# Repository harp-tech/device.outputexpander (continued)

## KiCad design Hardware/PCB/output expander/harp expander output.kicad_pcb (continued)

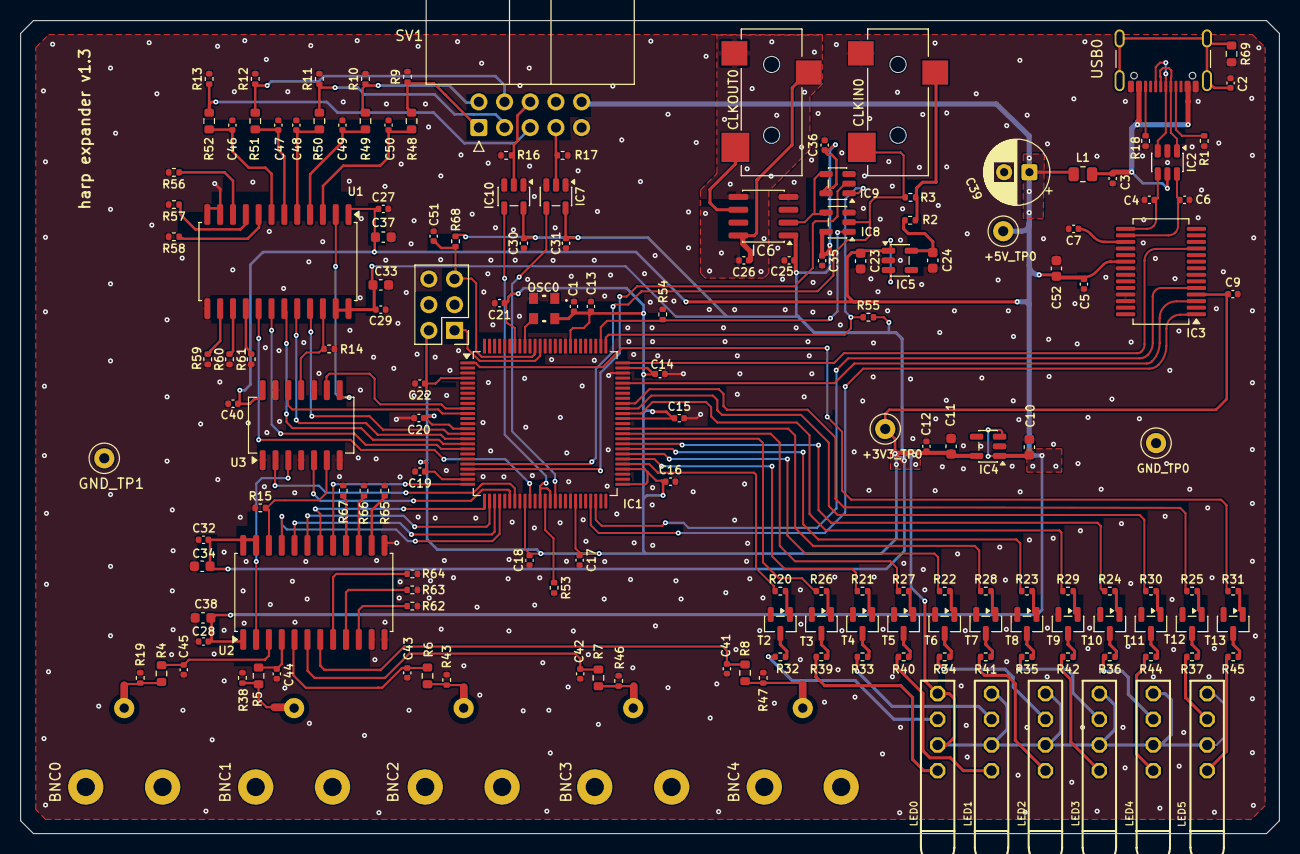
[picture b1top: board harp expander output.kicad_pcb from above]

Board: 2 copper layers, 124.5 x 80.4 mm, 167 parts (0 on the bottom side), 132 nets.

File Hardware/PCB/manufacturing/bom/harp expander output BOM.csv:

"#","Qty","Reference","Value","Tolerance","Footprint","TempCo","Voltage","DNP","OEPSPN","MPN"
"1","5","BNC0,BNC1,BNC2,BNC3,BNC4","731000105","","open-ephys:BNC_MOLEX_0731000105","","","","OEPS070024","731000105"
"2","27","C1,C3,C5,C7,C9,C12,C13,C14,C15,C16,C17,C18,C19,C20,C21,C22,C25,C26,C27,C28,C29,C30,C31,C32,C35,C36,C40","100nF","10%","Capacitor_SMD:C_0402_1005Metric","X7R","50V","","OEPS010016","CGA2B3X7R1H104K050BB"
"3","1","C2","4.7nF","10%","Capacitor_SMD:C_0402_1005Metric","X7R","100V","","OEPS010017","885012205084"
"4","2","C4,C6","47pF","5%","Capacitor_SMD:C_0402_1005Metric","C0G","50V","","OEPS010011","04025A470JAT2A"
"5","9","C10,C11,C23,C24,C33,C34,C37,C38,C52","4.7uF","10%","Capacitor_SMD:C_0603_1608Metric","X6S","16V","","OEPS010018","C1608X6S1C475K080AC"
"6","1","C39","100u","20%","Capacitor_THT:CP_Radial_D6.3mm_P2.50mm","","25V","","OEPS210005","EEU-FM1E101B"
"7","11","C41,C42,C43,C44,C45,C46,C47,C48,C49,C50,C51","330pF","5%","Capacitor_SMD:C_0402_1005Metric","C0G","50V","","OEPS010020","C0402C331J5GAC7867"
"8","2","CLKIN0,CLKOUT0","35RASMT2BHNTRX","","harp_expander_output:35RASMT2BHNTRX","","","","OEPS070025","35RASMT2BHNTRX"
"9","1","IC1","ATXMEGA128A1U-AU","","Package_QFP:TQFP-100_14x14mm_P0.5mm","","","","OEPS080083","ATXMEGA128A1U-AU"
"10","1","IC2","USBLC6-2SC6","","Package_TO_SOT_SMD:SOT-23-6","","","","OEPS030010","USBLC6-2SC6"
"11","1","IC3","FT232RL-REEL","","Package_SO:SSOP-28_5.3x10.2mm_P0.65mm","","","","OEPS080013","FT232RL-REEL"
"12","2","IC4,IC5","TLV70033DDCR","","Package_TO_SOT_SMD:SOT-23-5","","","","OEPS080086","TLV70033DDCR"
"13","1","IC6","SI8621BC-B-ISR","","Package_SO:SOIC-8_5.3x5.3mm_P1.27mm","","","","OEPS080031","SI8621BC-B-ISR"
"14","4","IC7,IC8,IC9,IC10","SN74LVC1G125DBVT","","Package_TO_SOT_SMD:SOT-23-5","","","","OEPS080029","SN74LVC1G125DBVT"
"15","1","L1","MI0805K400R-10","","Resistor_SMD:R_0805_2012Metric","","","","OEPS040003","MI0805K400R-10"
"16","6","LED0,LED1,LED2,LED3,LED4,LED5","569-0111-100F","","harp_expander_output:569-011X-X00_LED_ARRAY","","","","OEPS030007","569-0111-100F"
"17","1","OSC0","O 32,0-JT32C-A-K-3,3-LF","","harp_expander_output:OSCILLATOR_3.2X2.5","","","","OEPS080014","O 32,0-JT32C-A-K-3,3-LF"
"18","1","PDI0","67996-206HLF","","Connector_PinHeader_2.54mm:PinHeader_2x03_P2.54mm_Vertical","","","","OEPS070015","67996-206HLF"
"19","2","R1,R18","5.1k","1%","Resistor_SMD:R_0402_1005Metric","","","","OEPS020173","ERJ-2RKF5101X"
"20","1","R2","10R","5%","Resistor_SMD:R_0402_1005Metric","","","","OEPS020041","ERJ-PA2J100X"
"21","31","R3,R9,R10,R11,R12,R13,R14,R15,R16,R17,R19,R38,R43,R46,R47,R53,R54,R55,R56,R57,R58,R59,R60,R61,R62,R63,R64,R65,R66,R67,R68","10k","1%","Resistor_SMD:R_0402_1005Metric","","","","OEPS020030","CRCW040210K0FKED"
"22","11","R4,R5,R6,R7,R8,R48,R49,R50,R51,R52,R69","100R","1%","Resistor_SMD:R_0603_1608Metric","","","","OEPS020042","CRCW0603100RFKEAHP"
"23","12","R20,R21,R22,R23,R24,R25,R26,R27,R28,R29,R30,R31","1k","1%","Resistor_SMD:R_0402_1005Metric","","","","OEPS020027","CRCW04021K00FKED"
"24","12","R32,R33,R34,R35,R36,R37,R39,R40,R41,R42,R44,R45","330R","1%","Resistor_SMD:R_0402_1005Metric","","","","OEPS020037","RC0402FR-07330RL"
"25","1","SV1","SBH11-PBPC-D05-RA-BK","","Connector_IDC:IDC-Header_2x05_P2.54mm_Horizontal","","","","OEPS070027","SBH11-PBPC-D05-RA-BK"
"26","12","T2,T3,T4,T5,T6,T7,T8,T9,T10,T11,T12,T13","BC850C,215","","Package_TO_SOT_SMD:SOT-23","","","","OEPS060006","BC850C,215"
"27","2","U1,U2","SN74LVC4245APWR","","Package_SO:SOIC-24W_7.5x15.4mm_P1.27mm","","","","OEPS080126","SN74LVC4245APWR"
"28","1","U3","74HCT125D,653","","Package_SO:SO-14_5.3x10.2mm_P1.27mm","","","","OEPS080024","74HCT125D,653"
"29","1","USB0","USB4105-GF-A","","Connector_USB:USB_C_Receptacle_GCT_USB4105-xx-A_16P_TopMnt_Horizontal","","","","OEPS070105","USB4105-GF-A"

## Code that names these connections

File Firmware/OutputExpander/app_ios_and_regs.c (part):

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	io_pin2in(&PORTF, 1, PULL_IO_DOWN, SENSE_IO_EDGES_BOTH);             // PF1
	io_pin2in(&PORTF, 4, PULL_IO_DOWN, SENSE_IO_EDGES_BOTH);             // PF4
	io_pin2in(&PORTF, 5, PULL_IO_DOWN, SENSE_IO_EDGES_BOTH);             // PF5
	io_pin2in(&PORTF, 6, PULL_IO_DOWN, SENSE_IO_EDGES_BOTH);             // PF6
	io_pin2in(&PORTF, 7, PULL_IO_DOWN, SENSE_IO_EDGES_BOTH);             // PF7
	io_pin2in(&PORTJ, 3, PULL_IO_DOWN, SENSE_IO_EDGES_BOTH);             // PJ3
	io_pin2in(&PORTJ, 4, PULL_IO_DOWN, SENSE_IO_EDGES_BOTH);             // PJ4
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	io_pin2out(&PORTH, 7, OUT_IO_DIGITAL, IN_EN_IO_EN);                  // LED_7
	io_pin2out(&PORTJ, 0, OUT_IO_DIGITAL, IN_EN_IO_EN);                  // LED_8
	io_pin2out(&PORTJ, 1, OUT_IO_DIGITAL, IN_EN_IO_EN);                  // LED_9
	io_pin2out(&PORTJ, 2, OUT_IO_DIGITAL, IN_EN_IO_EN);                  // LED_PWR
	io_pin2out(&PORTA, 6, OUT_IO_DIGITAL, IN_EN_IO_EN);                  // LED_STATE
	io_pin2out(&PORTB, 5, OUT_IO_DIGITAL, IN_EN_IO_EN);                  // IDE_IOS_DIR
	io_pin2out(&PORTB, 6, OUT_IO_DIGITAL, IN_EN_IO_EN);                  // IDE_IOS_EN
	io_pin2out(&PORTD, 7, OUT_IO_DIGITAL, IN_EN_IO_EN);                  // BNC_IOS_DIR
	io_pin2out(&PORTD, 6, OUT_IO_DIGITAL, IN_EN_IO_EN);                  // BNC_IOS_EN
	io_pin2out(&PORTK, 1, OUT_IO_DIGITAL, IN_EN_IO_EN);                  // EN_CLOCK_OUT
	io_pin2out(&PORTK, 2, OUT_IO_DIGITAL, IN_EN_IO_EN);                  // EN_CLOCK_IN
	io_pin2out(&PORTD, 4, OUT_IO_DIGITAL, IN_EN_IO_EN);                  // OUT0
	io_pin2out(&PORTD, 3, OUT_IO_DIGITAL, IN_EN_IO_EN);                  // OUT1
	io_pin2out(&PORTD, 2, OUT_IO_DIGITAL, IN_EN_IO_EN);                  // OUT2
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
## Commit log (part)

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2020-10-31 Added gerbers, centroids and BOM.
2020-10-31 Added panels and production files.
2020-10-31 Added .gitignore.
2020-10-31 Created folders for Bonsai and Firmware.
2020-10-31 Added README and licenses.
2020-11-04 Corrected rear panel's silk screen.
2020-11-04 Added panels' gerber files.
2020-11-06 First firmware files.
2020-11-15 Added README files.
2020-11-15 Minor corrections.
2020-12-19 Added ability to connect to a Teensy/Arduino and to read rotary encoders.
2020-12-19 Added ability to be used as a clock generator.
2020-12-19 Minor corrections on layout and schematics.
2020-12-19 Updated BOM.
2020-12-19 Updated production files.
2020-12-20 Minor corrections to BOMs.
2021-01-02 Updated email address for commercial requests.
2021-01-29 Added pdf files and library.
2021-02-06 Updated for the first functional code (some features still to implement).
2021-02-06 Implemented LED management.
2021-02-07 Corrected visualization and implemented the magnetic encoder expansion.
2021-02-07 Added code to control the expander servo driver.
2021-02-11 Changed the audio cable PN.
2021-02-11 Replaced oscillator with a more precise one.
2021-02-16 Minor corrections to registers' descriptions.
2021-02-16 Corrected bad timing when using the servo expander.
2021-02-19 Updated license dates.
2021-02-21 Reversed the hardware's resistor assembly.
2021-02-21 Correct bad servo driver configuration.
2021-02-23 Added default for the magnetic encoder sample rate.
2021-03-04 Add Bonsai interface for harp expander devices
2021-03-07 Implemented ability to filter selected transitions on both auxiliary input lines.
2021-03-07 Added new registers to control PWM and stimulation.
2021-03-07 increased firmware version to 2.0.
2021-03-08 Created PWM and Stimulation registers.
2021-03-08 Renamed STIM registers and added PULSE registers.
2021-03-08 Added calculations for real frequency and duty cycle.
2021-03-08 Implemented the ability to produce up to 3 different PWMs.
2021-03-12 Fix #1.
2021-03-14 Fix register size
2021-03-15 Add pwm configuration and command support
2021-03-15 Extend support for pwm 1
2021-03-16 Added more flexibility to enable and disable PWM.
2021-03-19 Ensure existing PWM state is preserved
2021-03-21 Add interface for PWM event detection
2021-03-23 Add support for configuring expansion board modes
2021-03-23 Add support for parsing angle and intensity
2021-03-23 Add support for configuring magnetic encoder mode
2021-03-23 Ensure expression build methods are static
2021-03-23 Add support for configuring the remaining PWM
2021-04-24 Added filtering on inputs and reset lines to prevent erroneous behavior in noisy environments.
2021-04-24 Added a photo of the assembled device.
2021-04-27 Added ability to read a rotary encoder.
2021-05-13 Minor BOM correction.
2021-05-31 Updated harp core to version 1.9
2021-11-27 Mapped the clock enables in the IO list.
2022-05-04 Created SPI library.
2022-05-04 Created PAA5100JE optical tracking library.
2022-05-04 Implemented the optical tracking reading.
2022-05-04 Updated .gitignore.
2023-03-21 Changed projects to use Relative Paths.
2023-03-21 Updated Harp Core to version 1.12.
2023-03-21 Updated LICENSE.
2023-03-21 Added Bonsai workflows.
    These Bonsai workflows were used for tests.
2023-04-03 Updated panels to match PCB version.
2023-04-25 Add Assets directory
2023-04-25 Refactor repo structure to follow latest specs
2023-04-25 Fix README references
2023-04-25 Add dotnet template for automatic interface generation
2023-04-25 Add first draft of device schema
2023-04-25 Fix broken reference
2023-04-25 Add Device classes
2023-05-16 Update copyright notice
2023-06-01 Update schema to improve interface readability
2023-06-02 Update `Device` classes to the new schema
2023-06-07 Update mask name
2023-06-07 Update `Device` class
2023-06-07 Increment patch
2023-06-15 Add missing package metadata and interface license
2023-06-15 Add encoder and flow sensor payload metadata
2023-06-15 Bump interface version
2023-06-15 Rename encoder to magnetic encoder for consistency
2023-06-15 Rename to sample rate for consistency
2023-06-22 Regen interface to include timestamped payloads
2023-07-31 Update interface to use new generators
2023-08-03 Add missing package metadata for stable release
2023-08-10 Add .gitignore to Hardware
2023-08-10 Updated versions
2023-08-10 Replaced harp core 1.12 with 1.13.
2023-08-16 Add operator to configure PWM pulse train
2023-08-16 Add operator to configure magnetic encoder
2023-09-07 Added ability to avoid hardware check (for debug only).
2023-10-16 Fix register type
2023-12-01 Fix bit field values signalling input change
2023-12-03 Refactor PWM configuration to operate on channels
2023-12-03 Allow configuring trigger source and PWM events
2023-12-03 Bump prerelease suffix
2023-12-05 Update high-level interface
2024-04-03 Fix title heading
2024-05-15 Remove prerelease suffix
2024-11-09 Fix schema source
2024-11-09 Update generators and regenerate interface
2024-11-09 Fix package metadata to embed device metadata
2024-11-16 Favor harp-tech as source of device schema
2025-06-12 Create basic CI/CD for interface package
2025-10-22 Updated to atxmega core 1.15
2025-10-22 Updated firmware version to 2.3 in device.yml
2026-06-29 Moved Eagle to KiCAD:
2026-06-29 Moved panels from Eagle to KiCAD.
2026-06-29 Updated Gerbers.
